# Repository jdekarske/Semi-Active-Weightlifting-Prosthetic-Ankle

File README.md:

# README #
This repo contains any modeling, trials, and code related to SAWPA.

## Poster ##

### Contact ###
Jason Dekarske
jdekarske@ucdavis.edu

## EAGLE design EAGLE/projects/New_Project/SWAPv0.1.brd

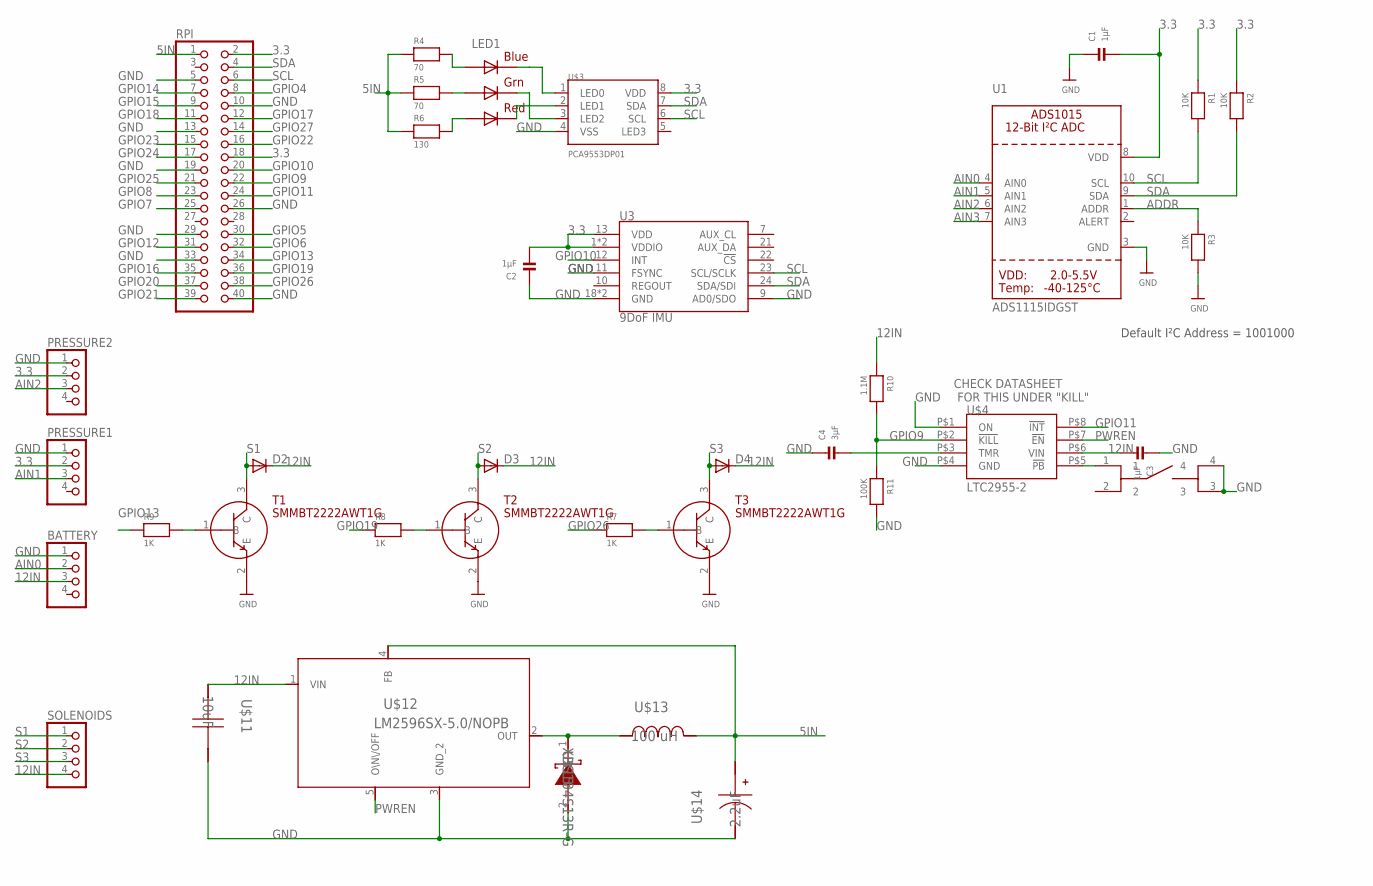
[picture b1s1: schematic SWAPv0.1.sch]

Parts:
BATTERY: JST_4PIN; JSTPH4
C1, C2, C3: 1µF; 1206
C4: 3µF; 1206
D2, D3, D4: DIODE-DO214AA; DO214AA
LED1: RGBLED5050
PRESSURE1, PRESSURE2: JST_4PIN; JSTPH4
R1, R2, R3: 10K; 2512
R4, R5: 70; 2512
R6: 130; 2512
R7, R8, R9: 1K; 2512
R10: 1.1M; 2512
R11: 100K; 2512
RPI: PINHD-2X20; 2X20
SOLENOIDS: JST_4PIN; JSTPH4
T1, T2, T3: SMMBT2222AWT1G; SOT323
U1: ADS1115IDGST; MSOP10
U3: 9DoF IMU; QFN24-3X3
U$3: PCA9553DP01; TSSOP8
U$4: LTC2955-2; TSOT23-8
U$10: B3FS-1015; B3FS
U$11: 10uF; 0805
U$12: LM2596SX-5.0/NOPB; TS5B
U$13: 100 uH; MSS1246T
U$14: 2.2uF; 3216-18
U$15: XBS104S13R-G; SOD-323

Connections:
3.3: C1.2, C2.2, PRESSURE1.2, PRESSURE2.2, R1.1, R2.1, RPI.2, RPI.18, U1.8 (VDD), U3.1 (VDDIO), U3.8 (VDDIO), U3.13 (VDD), U$3.8 (VDD)
5IN: R4.1, R5.1, R6.1, RPI.1, U$12.4 (FB), U$13.2, U$14.1 (+)
12IN: BATTERY.3, C3.2, D2.C, D3.C, D4.C, R10.1, SOLENOIDS.4, U$4.P$6 (VIN), U$11.2, U$12.1 (VIN)
ADDR: R3.1, U1.1 (ADDR)
AIN0: BATTERY.2, U1.4 (AIN0)
AIN1: PRESSURE1.3, U1.5 (AIN1)
AIN2: PRESSURE2.3, U1.6 (AIN2)
AIN3: U1.7 (AIN3)
GND: BATTERY.1, C1.1, C2.1, C3.1, C4.1, PRESSURE1.1, PRESSURE2.1, R3.2, R11.2, RPI.5, RPI.10, RPI.13, RPI.19, RPI.26, RPI.29, RPI.33, RPI.40, T1.2 (E), T2.2 (E), T3.2 (E), U1.3 (GND), U3.9 (AD0/SDO), U3.11 (FSYNC), U3.18 (GND), U3.20 (GND), U$3.4 (VSS), U$4.P$1 (ON), U$4.P$4 (GND), U$10.3, U$10.4, U$11.1, U$12.3 (GND_2), U$14.2 (-), U$15.2 (A)
GPIO4: RPI.8
GPIO5: RPI.30
GPIO6: RPI.32
GPIO7: RPI.25
GPIO8: RPI.23
GPIO9: R10.2, R11.1, RPI.22, U$4.P$2 (!KILL)
GPIO10: RPI.20, U3.12 (INT)
GPIO11: RPI.24, U$4.P$8 (!INT)
GPIO12: RPI.31
GPIO13: R9.1, RPI.34
GPIO14: RPI.7
GPIO15: RPI.9
GPIO16: RPI.35
GPIO17: RPI.12
GPIO18: RPI.11
GPIO19: R8.1, RPI.36
GPIO20: RPI.37
GPIO21: RPI.39
GPIO22: RPI.16
GPIO23: RPI.15
GPIO24: RPI.17
GPIO25: RPI.21
GPIO26: R7.1, RPI.38
GPIO27: RPI.14
unnamed: LED1.4 (BLUE_C), U$3.1 (LED0)
unnamed: LED1.5 (RED_C), U$3.2 (LED1)
unnamed: LED1.3 (BLUE_A), R4.2
unnamed: LED1.1 (GREEN_A), R5.2
unnamed: R9.2, T1.1 (B)
unnamed: LED1.2 (RED_A), R6.2
unnamed: R8.2, T2.1 (B)
unnamed: U$4.P$5 (!PB), U$10.1
unnamed: R7.2, T3.1 (B)
unnamed: C4.2, U$4.P$3 (TMR)
unnamed: LED1.6 (GREEN_C), U$3.3 (LED2)
unnamed: U$12.2 (OUT), U$13.1, U$15.1 (K)
PWREN: U$4.P$7 (!EN), U$12.5 (O\N\/OFF)
S1: D2.A, SOLENOIDS.1, T1.3 (C)
S2: D3.A, SOLENOIDS.2, T2.3 (C)
S3: D4.A, SOLENOIDS.3, T3.3 (C)
SCL: R1.2, RPI.6, U1.10 (SCL), U3.23 (SCL/SCLK), U$3.6 (SCL)
SDA: R2.2, RPI.4, U1.9 (SDA), U3.24 (SDA/SDI), U$3.7 (SDA)

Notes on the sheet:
Default I²C Address = 1001000
CHECK DATASHEET FOR THIS UNDER "KILL"

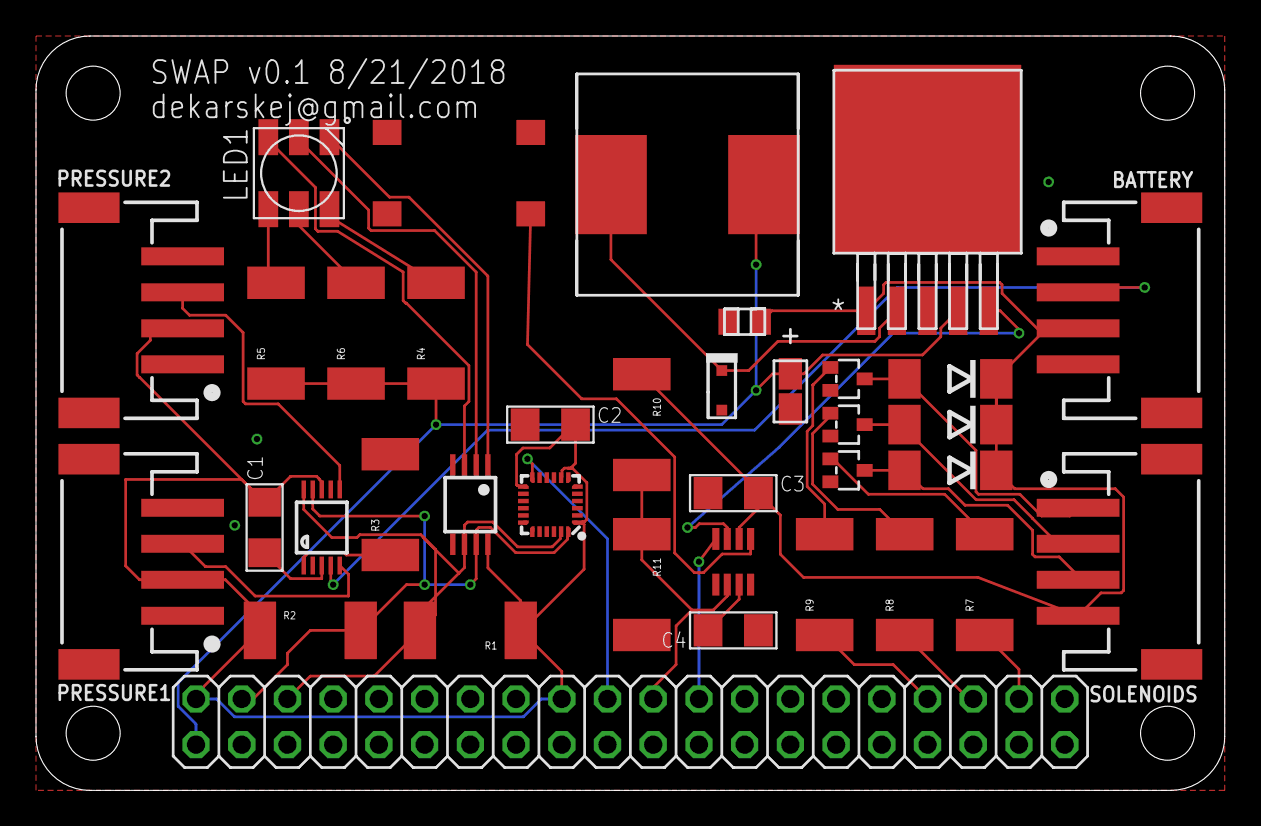
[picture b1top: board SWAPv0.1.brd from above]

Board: 2 copper layers, 66.0 x 41.9 mm, 37 parts (0 on the bottom side), 32 nets.

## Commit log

2017-09-21 Initial commit. AdamsquatV2 processes every file in a directory. Current version plots ankle moment by subject.
2017-09-21 README.md created online with Bitbucket
2017-11-10 initial raspi commit, bluetooth serial control working via controltesting.py
2017-12-05 menu functionality, streaming pressure data to phone
2018-01-23 poster session linear demo
2018-03-11 stable: Continuous menu framework bluetooth recovery LED state button handling missing: imu streaming calibration solenoid control
2018-12-20 update to current project state. This is from remote development done with PyCharm. Need to check if raspi code is consistent.
2019-01-10 Version 0.1 of the piHat for the ankle. Not sure about Git integration for Eagle, but it might work fine. Not sure how to turn this into an eagle "project"
    TODO:
    add gitignore
    replace transistors with uln2003 or similar (has flyback diode)
    LTC cap not connected to gnd
    switch C4 to 1uF for 5 second turnoff
    the LTC chip doesn't actually report single button presses on the INT pin. add latch circuit from the button to rpi gpio to read when using for menu changing or use the fourth input of PCA9553 as but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
2019-01-16 Reorganization
2019-01-17 support for PCA9553 LED driver and threading implementation. Untested, naturally. With the next board revision everything should be working better
2019-01-17 Forgot an important line

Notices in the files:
parts and their libraries:
SparkFun-Sensors: Licensing: Creative Commons ShareAlike 4.0 International - https://creativecommons.org/licenses/by-sa/4.0
